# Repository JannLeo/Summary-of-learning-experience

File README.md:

# 

# [icon]

# Name
# # Badge-徽章

*------ 备注：某些 READMEs 上，可能会看到小图像，例如项目是否通过了所有测试。可以使用*[护盾](http://shields.io/?fileGuid=2wAlXOVLNVUJQjAP)*在阅读器中添加说明。许多服务中也有添加徽章的说明。*

# ## Introduction-项目介绍

*------ 备注：让人们知道项目具体可以做什么。对阅读者任何可能不熟悉的地方，提供参考及访问链接；此处还可添加****功能列表****或****背景****的子菜单。如果有同类项目，应该在介绍中说明差异化、优势分析。*

## ### Summary-概要

## ### Features-特性

# ## Requirements-环境依赖

*------ 备注：环境，对所有项目，和所有子模块和库的描述。*

# ## Configuration-配置

*------ 备注：项目所需要的配置信息 。*

# ## Installation-安装

*------ 备注：如何安装，部署 ，最好包括界面操作截图及视频。*

# ## Usage-用法

*------ 备注：项目的入门使用方法 ，最好包括界面操作截图及视频*

# ## Development-开发

*------ 备注：关于怎样开发的文档信息，如 API 、兼容性等。*

# ## Changelog-更新日志

*------备注： 一个简短的历史记录，更改，替换或者其他。*

# ## FAQ-常见问题

*------备注： 常见的问题汇总，便于解决后续的新手答疑。*

# ## Support-支持

*------  备注：告诉用户可以去哪里寻求帮助。如问题跟踪器、聊天室、电子邮件地址等。*

## ### Doc-文档

*------ 备注：更多的文档说明 。*

## ### Release planning-版本规划

*------ 备注：对项目未来方向的规划。*

## ### Contact and Join-联系和加入社区

*------ 备注：可以包括但不限于如下条目*

* *用户社区的加入路径（微信/QQ/其它群二维码、项目助手的 ID等）*
* *项目的邮件订阅*
* *公司名称、网站、地址*
* *通过提交issue 联络解决遇到的问题*
# ## Contributing-贡献

*------ 备注：贡献指引。*

## ###  Contributors 贡献者

*----- 备注：作者列表和鸣谢。*

# ## License-版权信息

*------ 备注：版权、许可信息、法律声明。*

# ## Status 项目状态

*------ 备注：如果项目暂缓或停止更新，请进行状态标注。开发者可能会选择 fork 项目或自愿加入维护者或成为所有者，让其继续下去。同时，可在此处对维护者提出明确请求。*

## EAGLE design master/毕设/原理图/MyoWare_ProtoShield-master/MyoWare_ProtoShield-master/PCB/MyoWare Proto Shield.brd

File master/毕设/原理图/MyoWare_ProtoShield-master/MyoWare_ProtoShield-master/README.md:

# MyoWare_ProtoShield
Eagle files for the MyoWare™ Proto Shield

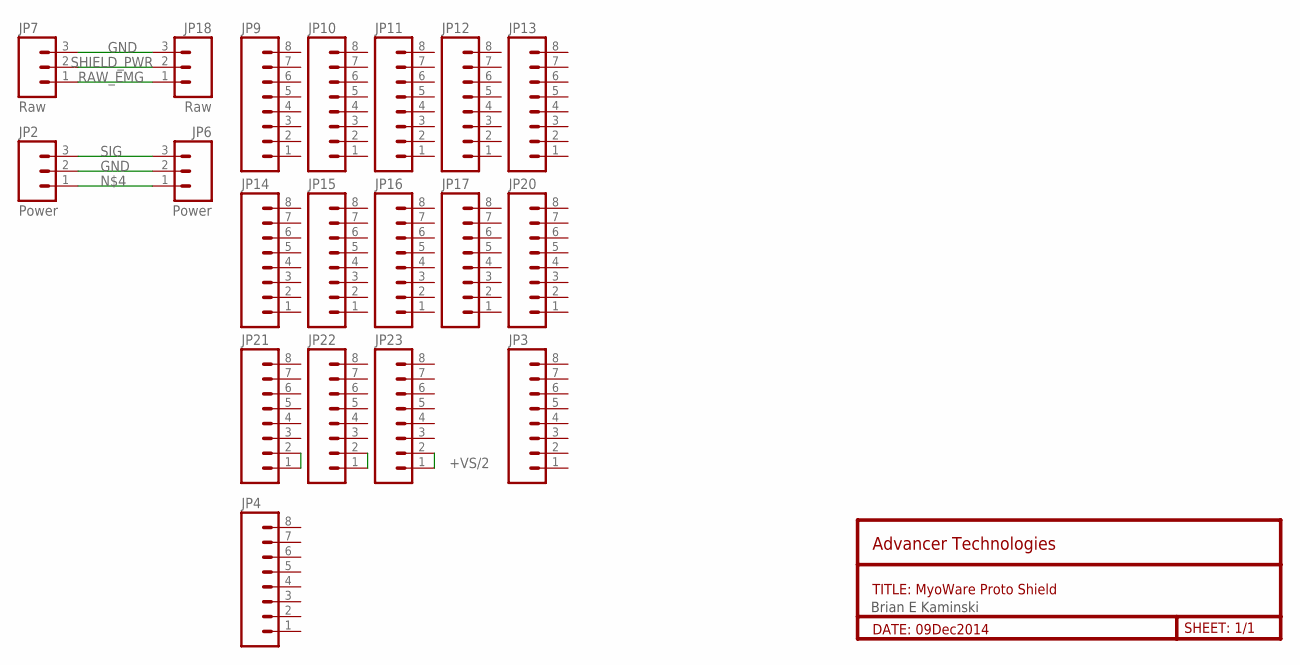
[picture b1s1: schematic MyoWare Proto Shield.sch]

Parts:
JP2, JP6: Power; 1X03_NO_SILK
JP3, JP4, JP9, JP10, JP11, JP12, JP13, JP14, JP15, JP16, JP17, JP20, JP21, JP22, JP23: M08NO_SILK; 1X08_NO_SILK
JP7, JP18: Raw; 1X03_NO_SILK

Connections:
+VS/2: JP23.1, JP23.2
GND: JP2.2, JP6.2, JP7.3, JP18.3
unnamed: JP21.1, JP21.2
unnamed: JP2.1, JP6.1
unnamed: JP22.1, JP22.2
RAW_EMG: JP7.1, JP18.1
SHIELD_PWR: JP7.2, JP18.2
SIG: JP2.3, JP6.3

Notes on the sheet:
Brian E Kaminski
TITLE: MyoWare Proto Shield
DATE: 09Dec2014
SHEET: 1/1
Advancer Technologies

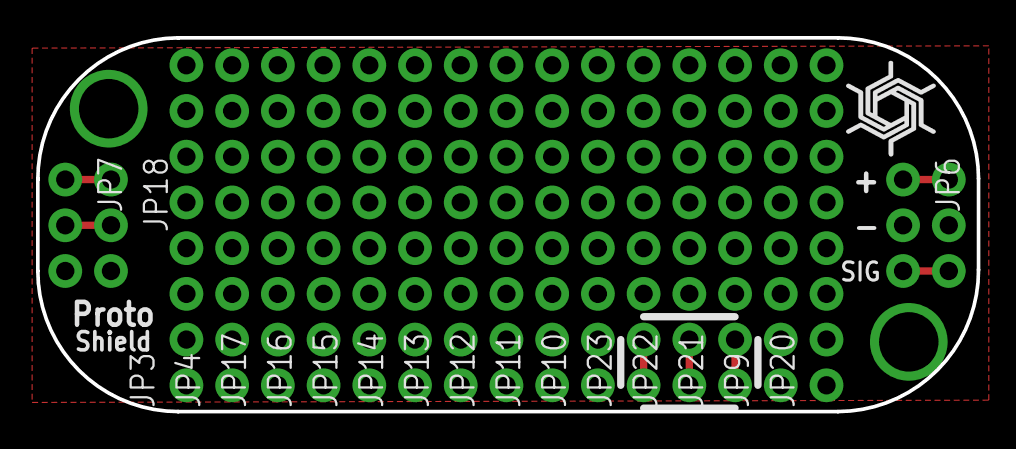
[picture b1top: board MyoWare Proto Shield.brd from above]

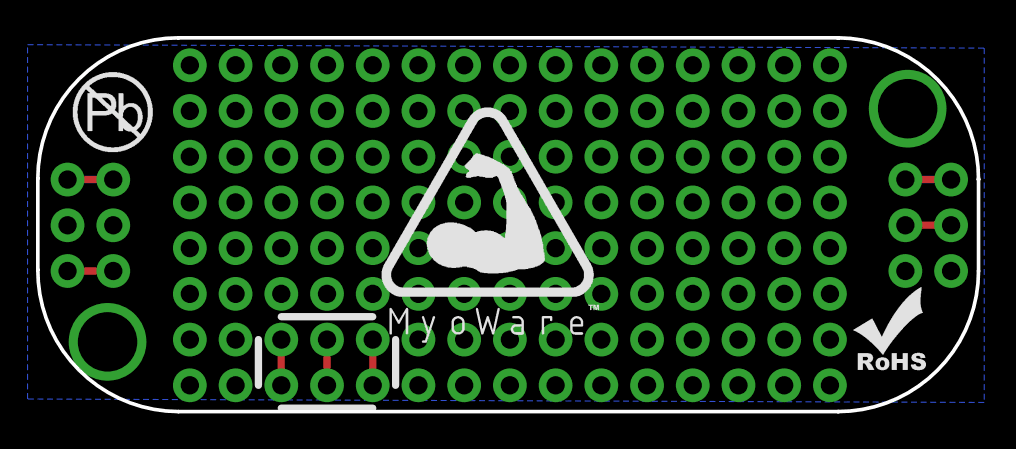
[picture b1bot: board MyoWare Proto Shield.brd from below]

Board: 2 copper layers, 52.3 x 20.8 mm, 23 parts (3 on the bottom side), 8 nets.

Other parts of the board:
U$1: MYOWARE_LOGO
U$3: ROHS
U$5: PB-FREE
U$9: SPIRAL_LOGO_60%

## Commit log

2023-12-06 leetcode_20230612
2023-12-07 10th day
2023-12-07 大二上资料
2023-12-08 Add .gitignore file
2023-12-08 51单片机学习
2023-12-09 231209 leetcode
2023-12-10 计算机系统
2023-12-10 计算机系统2
2023-12-11 计算机网络
2023-12-16 计算机论题
2023-12-18 算法导论
2023-12-21 java
2023-12-29 leetcode
2023-12-30 国外形式与政策
2023-12-31 一生一芯
2023-12-31 Use Git LFS for large files
2023-12-31 Stop tracking large files with Git LFS
2024-01-03 test
2024-01-07 leetcode-0107
2024-01-08 0118
2024-01-09 并行计算
2024-01-12 leetcode0112
2024-01-24 day23
2024-01-26 day23.5
2024-01-28 day24.5
2024-01-28 gitignore
2024-01-28 autopush
2024-01-30 test1
2024-02-09 09022024

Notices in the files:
parts and their libraries:
SparkFun-Connectors: Licensing: CC v3.0 Share-Alike You are welcome to use this library for commercial purposes.
